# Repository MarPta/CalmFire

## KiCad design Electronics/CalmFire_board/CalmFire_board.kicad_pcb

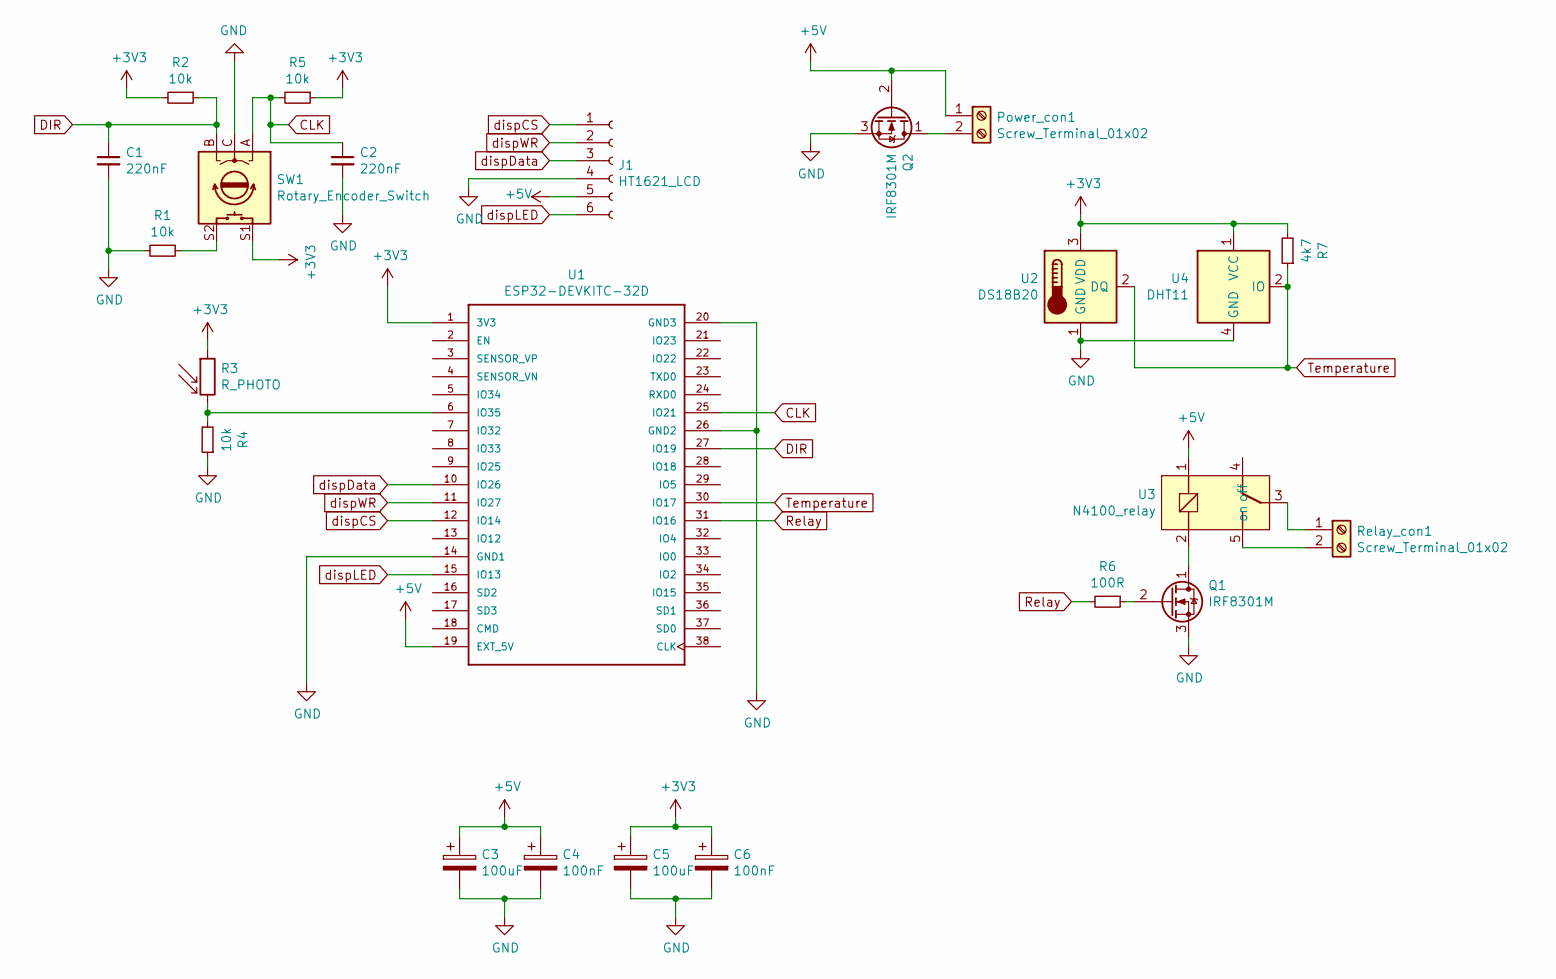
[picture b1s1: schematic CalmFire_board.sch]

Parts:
C1, C2: 220nF; C_Disc_D3.0mm_W1.6mm_P2.50mm
C3, C5: 100uF; CP_Radial_D6.3mm_P2.50mm
C4, C6: 100nF; C_Disc_D3.0mm_W1.6mm_P2.50mm
J1: HT1621_LCD; ht1621
Power_con1: Screw_Terminal_01x02; PhoenixContact_MC_1,5_2-G-5.08_1x02_P5.08mm_Horizontal
Q1, Q2: IRF8301M; TO-220-3_Vertical
R1, R2, R4, R5: 10k; R_Axial_DIN0207_L6.3mm_D2.5mm_P10.16mm_Horizontal
R3: R_PHOTO; R_LDR_5.0x4.1mm_P3mm_Vertical
R6: 100R; R_Axial_DIN0207_L6.3mm_D2.5mm_P10.16mm_Horizontal
R7: 4k7; R_Axial_DIN0207_L6.3mm_D2.5mm_P10.16mm_Horizontal
Relay_con1: Screw_Terminal_01x02; PhoenixContact_MC_1,5_2-G-5.08_1x02_P5.08mm_Horizontal
SW1: Rotary_Encoder_Switch; RotaryEncoder_Alps_EC11E-Switch_Vertical_H20mm
U1: ESP32-DEVKITC-32D; MODULE_ESP32-DEVKITC-32D
U2: DS18B20; TO-92_Inline
U3: N4100_relay
U4: DHT11; Aosong_DHT11_5.5x12.0_P2.54mm

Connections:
+3V3: C5.1, C6.1, R2.2, R3.1, R5.1, R7.2, SW1.S1, U1.1 (3V3), U2.3 (VDD), U4.1 (VCC)
+5V: C3.1, C4.1, J1.5, Power_con1.1, Q2.2 (G), U1.19 (EXT_5V), U3.1
CLK: C2.1, R5.2, SW1.A, U1.25 (IO21)
DIR: C1.1, R2.1, SW1.B, U1.27 (IO19)
GND: C1.2, C2.2, C3.2, C4.2, C5.2, C6.2, J1.4, Q1.3 (S), Q2.3 (S), R1.2, R4.1, SW1.C, U1.14 (GND1), U1.20 (GND3), U1.26 (GND2), U2.1 (GND), U4.4 (GND)
unnamed: Power_con1.2, Q2.1 (D)
unnamed: Q1.1 (D), U3.2
unnamed: Q1.2 (G), R6.1
unnamed: R1.1, SW1.S2
unnamed: R3.2, R4.2, U1.6 (IO35)
unnamed: Relay_con1.1, U3.3
unnamed: Relay_con1.2, U3.5 (on)
Relay: R6.2, U1.31 (IO16)
Temperature: R7.1, U1.30 (IO17), U2.2 (DQ), U4.2 (IO)
dispCS: J1.1, U1.12 (IO14)
dispData: J1.3, U1.10 (IO26)
dispLED: J1.6, U1.15 (IO13)
dispWR: J1.2, U1.11 (IO27)

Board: 2 copper layers, 23 parts (0 on the bottom side), 18 nets, no tracks yet.

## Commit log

2019-05-01 Transfer of repository.
2019-05-01 Cleaning. Correction of variables ranges. Storing desired temperature variables using Preferences instead of EEPROM class.
2019-05-02 Added support for MQTT publishing.
2019-05-02 Using quadratic encoder with encoder class for setting temperature.
2019-05-02 Basic schematic of CalmFire board.
2019-05-18 [Electronics] Updated schematic, created project library with relay schematic & footprint. Schematic complete, PCB ready to deploy.
2019-05-20 Created ht1621 display footprint. Added power capacitors, power polarity protection N-MOS. Changed temp sensors power to 3.3V and a pull-up on onewire.
2022-12-14 Removed internet connectivity. Fixed compilation.
2022-12-14 Regulating temp using buttons.
2022-12-15 Blynk demo
2022-12-15 Adafruit IO demo.
2022-12-16 Publishing mesuredTemp via Adafruit_MQTT
2022-12-18 MQTT thermostat demo
2023-01-15 Changed display for Nokia 84x48 LCD.
2023-01-15 Displaying heatMode and heatOn status.
